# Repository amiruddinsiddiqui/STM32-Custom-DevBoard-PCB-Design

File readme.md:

# STM32 Custom Development Board

A custom STM32F401 development board designed in KiCad, featuring USB connectivity, SWD debugging, and dedicated peripheral headers.

## 3D PCB View

## PCB Layout

## Schematic

## Features

- **Microcontroller:** STM32F401
- **USB Connectivity:** USB connector for power
- **Debugging:** SWD header for programming and debugging
- **Boot Configuration:** BOOT selection switch
- **Communication Interfaces:** UART2, SPI1, and I2C1 headers
- **Power Supply:** USB VBUS to 3.3V regulation
- **PCB Design:** Two-layer PCB designed using KiCad

## Tools Used

- KiCad 10

## Repository Contents

- KiCad schematic and project files
- PCB layout
- Design preview images
---

Designed by ```Amiruddin```

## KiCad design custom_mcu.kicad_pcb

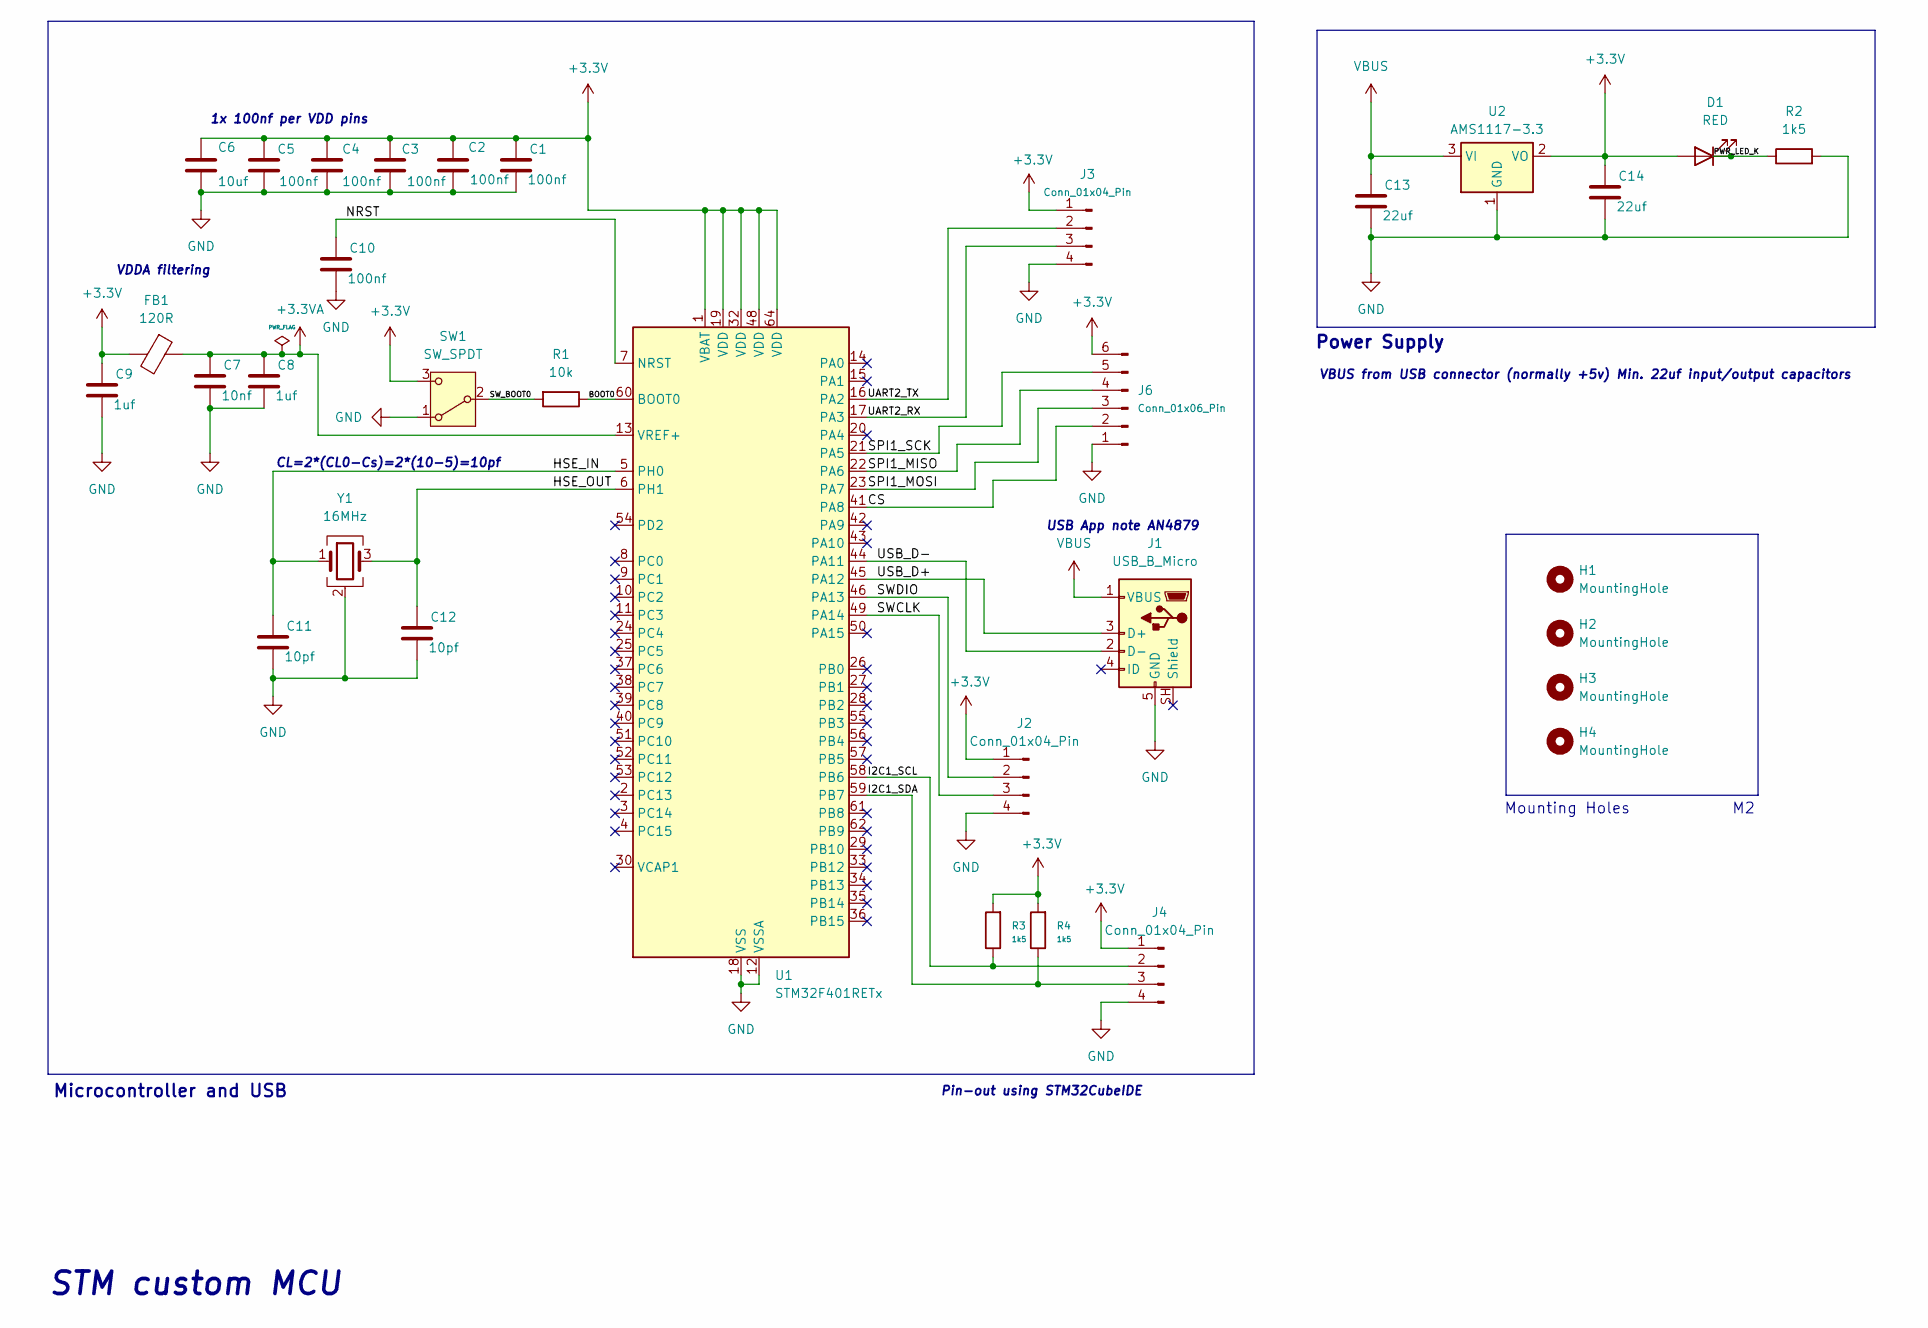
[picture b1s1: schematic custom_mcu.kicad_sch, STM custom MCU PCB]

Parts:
C1, C2, C3, C4, C5, C10: 100nf; C_0402_1005Metric
C6: 10uf; C_0603_1608Metric
C7: 10nf; C_0402_1005Metric
C8, C9: 1uf; C_0402_1005Metric
C11, C12: 10pf; C_0402_1005Metric
C13, C14: 22uf; C_0805_2012Metric
D1: RED; LED_0603_1608Metric
FB1: 120R; L_0603_1608Metric
H1, H2, H3, H4: MountingHole; MountingHole_2.2mm_M2
J1: USB_B_Micro; USB_Micro-B_Molex_47346-0001
J2, J3, J4: Conn_01x04_Pin; PinHeader_1x04_P2.54mm_Vertical
J6: Conn_01x06_Pin; PinHeader_1x06_P2.54mm_Vertical
R1: 10k; R_0402_1005Metric
R2, R3, R4: 1k5; R_0402_1005Metric
SW1: SW_SPDT; SW_SPDT_PCM12
U1: STM32F401RETx; LQFP-64_10x10mm_P0.5mm
U2: AMS1117-3.3; SOT-223-3_TabPin2
Y1: 16MHz; Crystal_SMD_3225-4Pin_3.2x2.5mm

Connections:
+3.3V: C1.1, C2.1, C3.1, C4.1, C5.1, C6.1, C9.1, C14.1, D1.2 (A), FB1.2, J2.1, J3.1, J4.1, J6.6, R3.2, R4.2, SW1.3 (C), U1.1 (VBAT), U1.19 (VDD), U1.32 (VDD), U1.48 (VDD), U1.64 (VDD), U2.2 (VO)
+3.3VA: C7.1, C8.1, FB1.1, U1.13 (VREF+)
/BOOT0: R1.1, U1.60 (BOOT0)
/CS: J6.2, U1.41 (PA8)
/HSE_IN: C11.1, U1.5 (PH0), Y1.1
/HSE_OUT: C12.1, U1.6 (PH1), Y1.3
/I2C1_SCL: J4.2, R3.1, U1.58 (PB6)
/I2C1_SDA: J4.3, R4.1, U1.59 (PB7)
/NRST: C10.1, U1.7 (NRST)
/PWR_LED_K: D1.1 (K), R2.1
/SPI1_MISO: J6.4, U1.22 (PA6)
/SPI1_MOSI: J6.3, U1.23 (PA7)
/SPI1_SCK: J6.5, U1.21 (PA5)
/SWCLK: J2.3, U1.49 (PA14)
/SWDIO: J2.2, U1.46 (PA13)
/SW_BOOT0: R1.2, SW1.2 (B)
/UART2_RX: J3.3, U1.17 (PA3)
/UART2_TX: J3.2, U1.16 (PA2)
/USB_D+: J1.3 (D+), U1.45 (PA12)
/USB_D-: J1.2 (D-), U1.44 (PA11)
GND: C1.2, C2.2, C3.2, C4.2, C5.2, C6.2, C7.2, C8.2, C9.2, C10.2, C11.2, C12.2, C13.2, C14.2, J1.5 (GND), J2.4, J3.4, J4.4, J6.1, R2.2, SW1.1 (A), U1.12 (VSSA), U1.18 (VSS), U1.31 (VSS), U1.47 (VSS), U1.63 (VSS), U2.1 (GND), Y1.2 (G), Y1.4 (G)
VBUS: C13.1, J1.1 (VBUS), U2.3 (VI)

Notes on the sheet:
Mounting Holes
1x 100nf per VDD pins
CL=2*(CL0-Cs)=2*(10-5)=10pf
USB App note AN4879
Microcontroller and USB
VDDA filtering
VBUS from USB connector (normally +5v) Min. 22uf input/output capacitors
Pin-out using STM32CubeIDE
Power Supply
STM custom MCU

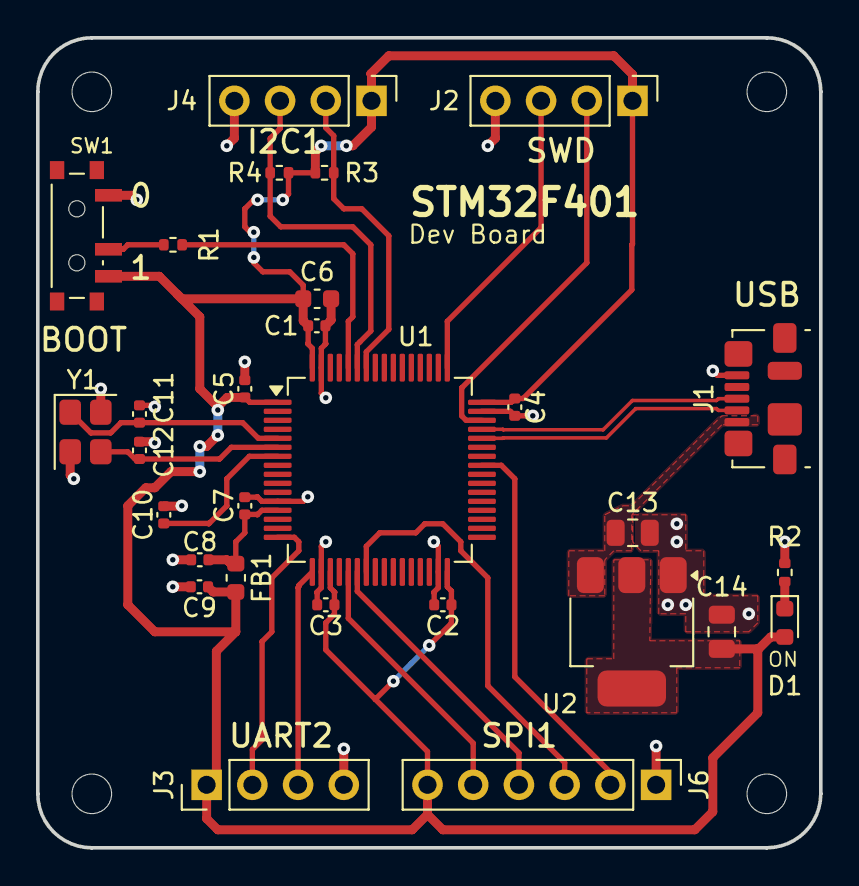
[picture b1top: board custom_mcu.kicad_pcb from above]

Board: 2 copper layers, 43.5 x 45.0 mm, 33 parts (0 on the bottom side), 22 nets.
